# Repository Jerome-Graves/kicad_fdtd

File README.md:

# kicad_fdtd

A GPU field solver for KiCad boards. Point it at any `.kicad_pcb`: it pulls the exact copper
(pads, tracks, zone fills, vias, outline, stackup) through KiCad's own geometry engine, meshes
the nets you care about, checks the model before it spends a second of GPU time, and gives you
S-parameters, impedance and a field view in a browser. Written in Python with NumPy and CuPy;
no openEMS, no black box.

```
kicad-fdtd stats   my_board.kicad_pcb                      # what is on the board
kicad-fdtd pair    my_board.kicad_pcb /USB_DP /USB_DM --ports J1.A6 U5.1 J1.A7 U5.3
kicad-fdtd thermal my_board.kicad_pcb --power U1=0.5 U3=0.3 --net /3V3 --from U3.4 --to J8.1 --current 1
kicad-fdtd gui                                             # everything above in a browser
```

## In the browser, no install

**https://jeromegraves.com/kicad_fdtd/** runs the whole tool on your own machine: drop a
`.kicad_pcb` on the page (nothing is uploaded), get the stats, pick nets and pads, mesh and
check, run the field solver on your GPU through WebGPU (Chrome or Edge; other browsers fall
back to a slow JavaScript engine), and solve thermal and IR drop. The browser build in
`docs/app/` is a line-for-line port of the Python package: its own `.kicad_pcb` reader
(checked against pcbnew's polygons on real boards, pad positions to the micron), the same
mesh, edge assignment and merge check, the same six kernels in WGSL, and the same
finite-volume thermal/DC solver. On the same board and mesh it returns the same Zdiff as the
Python/CuPy solver and runs at the same speed (3.2 Gcell-updates/s on an RTX 4070).
`docs/selftest.html?board=...&nets=...&ports=...` runs the pipeline headlessly;
`tests/web/*.mjs` compare the JavaScript modules with the Python results.

## Why

Every field solver hides the same three failure modes: copper assigned to the wrong
conductor on the mesh, absorbing boundaries touching the board, ports sitting on the wrong
copper. In a black box each one costs an hour of simulation before you find out. Here the
physics is a few hundred lines you can read, every mesh edge's owner is visible in the GUI,
and a merge check refuses to solve a model where two conductors touch. On an RTX 4070 a
5 Mcell board mesh runs at 3.2 Gcell-updates per second, so a USB pair at 0.1 mm resolution
takes about a minute.

## Install

```
git clone https://github.com/Jerome-Graves/kicad_fdtd
cd kicad_fdtd
python -m venv venv && venv\Scripts\activate          # or source venv/bin/activate
pip install -e .[gpu]                                 # NumPy, shapely, CuPy for CUDA 12
```

Without a CUDA GPU use `pip install -e .` and add `--cpu` to `pair`; the solver falls back to
NumPy (correct, roughly 100 times slower). KiCad 7 or later must be installed: the exporter
runs inside KiCad's bundled Python (found automatically on Windows and macOS; on Linux the
distro package puts `pcbnew` in the system Python). Set `KICAD_PYTHON` if it is somewhere else.

## Use

**Stats.** `kicad-fdtd stats board.kicad_pcb` prints size, stackup (from the file, or a
1.6 mm FR4 default with a warning), copper area and fill per layer, footprint/pad/via/net
counts, the reference net (the net with the most zone copper, usually GND) and the
differential pairs it can recognise by name. `--json` adds per-net detail.

**Pair or single net.** `kicad-fdtd pair board.kicad_pcb NET_P [NET_N] --ports REF.PAD ...`
Ports are pad names: P start, P stop, then N start, N stop. Each port is a lumped Z0
resistor with a source between the signal copper and the nearest reference copper under
it; the whole port face has to sit on the right copper on both layers or the tool says so.
Two nets are solved in odd mode (Zdiff = 2 Zodd, S11dd, S21dd), one net single-ended.
Options: `--res` fine cell (mm, default 0.1), `--base` coarse cell, `--fmax`, `--z0`,
`--ref NET` to override the reference net, `--tie NET ...` to treat other nets as reference
copper (a decoupled rail), `--setup-only` to stop after the checks, `--bench N` for speed.

**Thermal and DC.** `kicad-fdtd thermal board.kicad_pcb --power REF=W ... [--h 10] [--tamb 25] [--cell 0.25]`
solves steady-state heat conduction on a whole-board grid built from the same exact copper:
each copper layer is a thin sheet with conductivity scaled by its copper fraction per cell,
FR4 is anisotropic (0.8 W/mK in plane, 0.3 through), via barrels conduct through the planes,
component power goes into the cells under the footprint's pads, and both faces lose heat by
convection `h` to `--tamb` (edges adiabatic, no radiation, nothing above the board: a
conservative estimate). Add `--net NET --from REF.PAD --to REF.PAD --current A` for a DC
conduction solve on one net: IR drop, resistance, current density per cell, and the Joule
heat, which is added to the thermal sources. Output: a report (max temperature and where,
per-layer maxima, hottest footprints, drop and peak current density) and a JSON with the
temperature, voltage and current-density maps per copper layer.

**Examples with presets (web app).** The *Examples* menu loads a board and fills every panel:
the demo board (`docs/examples/demo.kicad_pcb`, 4 layers, a 100 Ω clock pair from a connector
to an MCU, a single-ended clock line to a header, an LDO feeding the MCU through a 3V3 pour on
In2, two heat sources) in a signal-integrity preset and an emissions preset, the microstrip
milestone, and the patch antenna. `?example=demo-pair` in the URL does the same.

**GUI.** `kicad-fdtd gui` then open http://127.0.0.1:8765. Paste a `.kicad_pcb` path and
press Import (or pick an already exported board), read the stats, pick nets (the detected
pairs are one click), click pads for ports, **Set up and check**. The view shows the mesh
window, the mesh, the PEC edge assignment per conductor on any copper layer, the port sites
and any shorts (red rings; Run stays disabled). **Run on GPU** streams progress, keeps Ez
snapshots on the plane under the first port (slider, play) and plots S11/S21 and Zin/Zdiff.
The **Thermal and DC** panel takes component powers (REF=W per line), h, ambient, cell size
and an optional DC net with source and sink pads; the result overlays temperature, current
density or DC voltage on any copper layer with a colour bar.

**Emissions (far field).** Tick *compute the far field* before *Set up*: the whole board is
meshed with an air gap around it, and during the run the tangential fields on a Huygens box
in that gap are transformed to the far field (equivalent currents, peak over a sphere, 3 m).
The result is the field per volt driven into port 1 at each frequency, the harmonics of a
trapezoid clock you specify (frequency, amplitude, rise time, duty) in dBµV/m against the
CISPR 32 class B limit, and a plot. The report also prints radiated over accepted power per
frequency: on a lossless board it must be close to 1 where the board accepts power; if it is
well below 1 the run stopped before the ring-down ended (raise t max). 

Validation: a patch
antenna example (`docs/examples/patch.kicad_pcb`) gives 1.00 to 1.06 across its resonance,
and the port bookkeeping balances the field energy in a closed box to 0.3 %
(`tests/web/check_energy.mjs`, `tests/web/check_flux.mjs`). Caveats: the source spectrum is
a clean trapezoid on one net (common-mode paths through cables and the rest of the product
are not modelled), and the limit compared is the peak-detector line, so a pass here is a
necessary condition, not a certification.

## How it works

```
kicad_fdtd/
  export.py     KiCad's Python (pcbnew) -> geometry.json: exact polygons, vias, pads, stackup
  geometry.py   model frame (y up, z from top copper), stackup defaults, reference net,
                port sites, board stats, differential pair detection
  mesh.py       rectilinear mesh: lines on the copper edges of the nets of interest,
                neighbours' edges within 0.6 mm, base grid, graded air cells; CFL step
  voxel.py      every Yee edge assigned to a conductor by an exact polygon test at the
                edge midpoint (sheets) or cylinder (vias); merge_check finds shared nodes
  solver.py     Yee FDTD on a non-uniform grid, CPML on six faces, PEC edges, lumped ports,
                energy-based end criterion; NumPy fallback
  kernels.py    six fused CuPy kernels (curl, CPML and ports in one launch each),
                port V/I read by one kernel; no host sync inside the step loop
  pair.py       setup (mesh + assignment + checks) and solve (S-parameters, Z)
  thermal.py    whole-board finite-volume grid from the same copper; steady-state heat
                conduction with convection faces; DC conduction on one net (IR drop, J,
                Joule heat); Jacobi-preconditioned CG on the GPU (cupyx) or CPU (scipy)
  cli.py        export | stats | pair | thermal | gui | test
  gui/          standard-library server + one page
tests/          test_msl.py (microstrip milestone, GPU), test_geometry.py and
                test_thermal.py (analytic checks, no GPU)
```

Field quantities are float32; V and I are recorded on the device each step and transformed
at the end. `FDTD_PROFILE=1` prints a per-section time breakdown, `FDTD_UNFUSED=1` runs the
slice-based reference path.

## Validation

| case | this solver | reference |
|---|---|---|
| 0.2 mm microstrip over 0.1 mm FR4, 50 Ω ports (`tests/test_msl.py`) | S21 −0.06 dB, S11 −18.6 dB, Zin 42 Ω | openEMS 43 Ω, 2D FD cross-section 45 Ω |
| USB pair on a 4-layer board, 0.15 mm vs 0.1 mm mesh | Zdiff 58 Ω vs 60 Ω | 2D FD cross-section 66 Ω |
| fused kernels vs slice reference vs pre-fusion code, same mesh | identical step count, S-parameters equal to 1e-6 dB | |
| copper-clad plate, 1 W, h = 10 W/m²K both faces (`tests/test_thermal.py`) | mean rise 319.6 K | lumped P / (2 h A) = 312.5 K |
| 0.2 mm × 35 µm track, 1 A over 11.4 mm | 27.7 mV, Joule = I·V | ρ L / (w t) = 27.4 mV |
| 4-layer 40 mm board, 1.4 W in six parts, natural convection | mean rise 44 K, 79 °C at the charger | P / (2 h A) = 44 K |
| browser build vs Python: USB pair, same 0.15 mm mesh | Zdiff 58 Ω, 3.2 Gcell/s (WebGPU) | Zdiff 58 Ω, 3.2 Gcell/s (CuPy) |
| browser build vs Python: thermal and DC on the same board | 79.2 °C, 7.8 mV | 78.9 °C, 7.8 mV |
| lumped port energy vs field energy, closed PEC box, patch example | equal to 0.3 % over 2.5 ns | energy conservation |
| far field: radiated vs accepted power, patch at 1.78 to 1.90 GHz, 80 ns window | 1.00 to 1.06 | 1 (lossless) |

The milestone runs in about a second on the GPU and is the regression gate for every
change to the solver.

## Limits

- Copper is perfect (PEC) and infinitely thin. Conductor and dielectric loss are on the list.
- Only the copper of the selected nets and their neighbours within 0.6 mm is meshed finely;
  the rest of the board is on the base grid. Parts (bodies, connectors) are not modelled.
- Ports need reference copper under the pad; a trace with no plane below gets no port.
- Stackups without thicknesses fall back to 1.6 mm FR4 split evenly.
- Thermal is steady state with a uniform convection coefficient and no radiation, no
  enclosure, no component bodies: it ranks hot spots and gives a conservative rise, not a
  datasheet junction temperature. Current density is per grid cell, so a narrow neck is
  averaged over the cell (use `--cell 0.1` for tracks).

## Roadmap

- Transient thermal and a component thermal-resistance model (junction to board).
- Far field in the Python package too (today it is in the browser build only).
- Conducting-sheet loss, dielectric loss.
- Whole-board mesh presets and a results archive in the GUI.

## Contributing

See [CONTRIBUTING.md](CONTRIBUTING.md). MIT licensed.

Written while designing the boards for [BugBot](https://www.bugbotlab.com/), a small robot for teaching robotics
and computer science.

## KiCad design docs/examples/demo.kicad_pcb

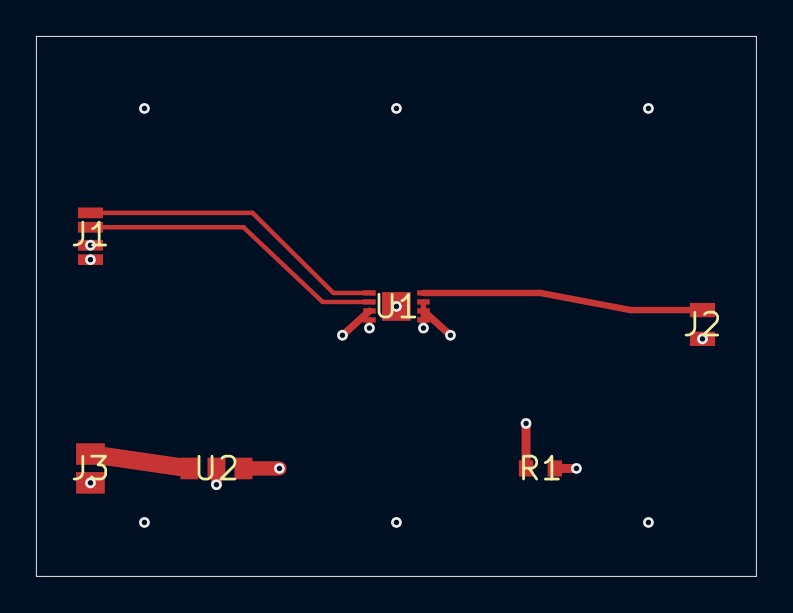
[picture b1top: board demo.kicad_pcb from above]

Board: 4 copper layers, 40.0 x 30.0 mm, 6 parts (0 on the bottom side), 6 nets.

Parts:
J1: clock in, 100 ohm pair; conn4
J2: clock out; header2
J3: power in; pwr2
R1: load; r0603
U1: MCU; qfn8
U2: LDO 3V3; sot23

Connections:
/3V3: R1.1, U1.3, U1.7, U2.3
/CLKOUT: J2.1, U1.5
/CLK_N: J1.2, U1.2
/CLK_P: J1.1, U1.1
/VIN: J3.1, U2.1
GND: J1.3, J1.4, J2.2, J3.2, R1.2, U1.4, U1.6, U1.8, U1.9, U2.2

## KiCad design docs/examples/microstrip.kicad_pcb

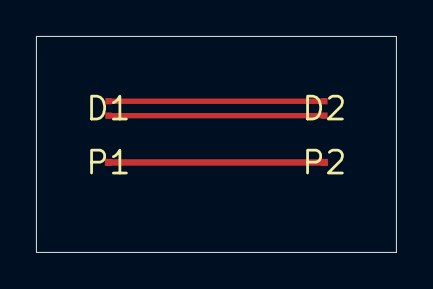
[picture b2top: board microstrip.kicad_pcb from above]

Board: 2 copper layers, 20.0 x 12.0 mm, 4 parts (0 on the bottom side), 3 nets.

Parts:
D1, D2: pair
P1, P2: port

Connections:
/CLK_N: D1.2, D2.2
/CLK_P: D1.1, D2.1
/SIG: P1.1, P2.1
